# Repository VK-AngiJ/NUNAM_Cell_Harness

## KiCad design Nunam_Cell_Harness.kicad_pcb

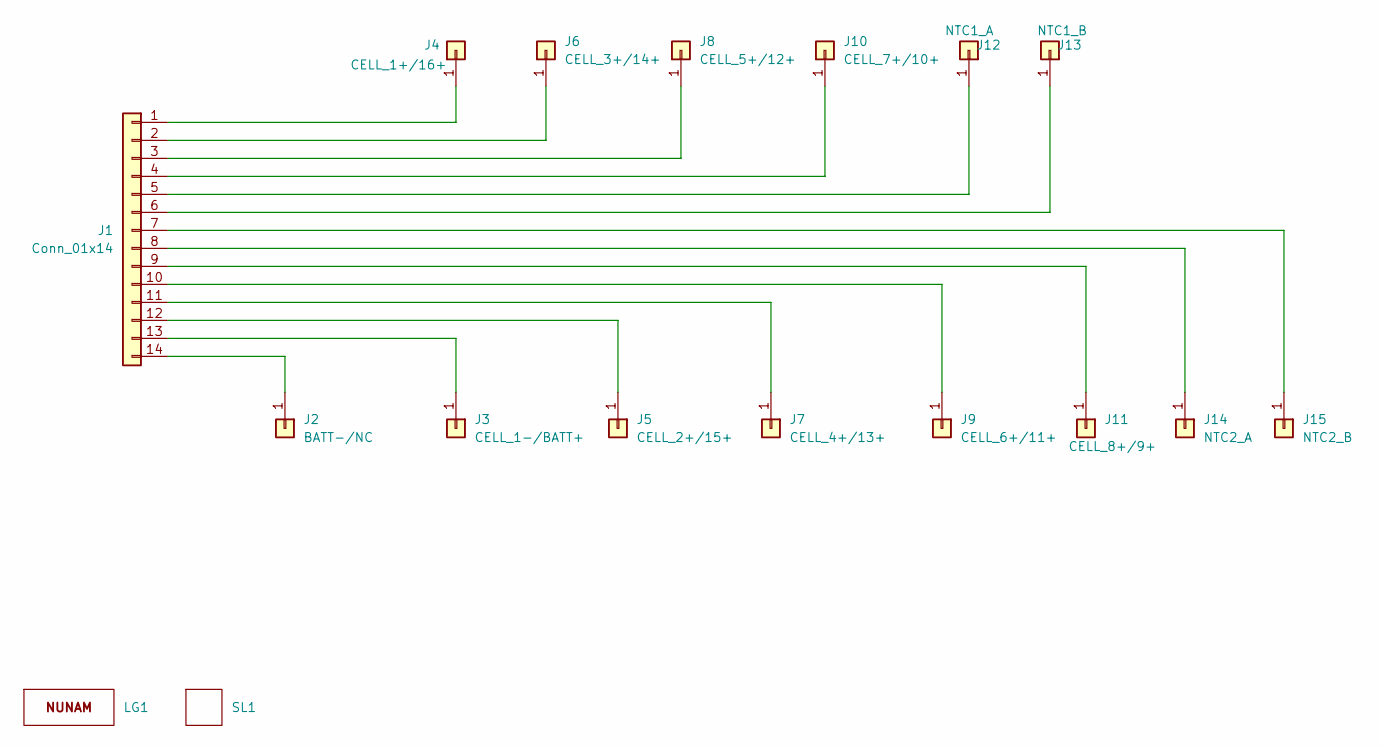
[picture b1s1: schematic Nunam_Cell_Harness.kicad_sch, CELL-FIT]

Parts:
J1: Conn_01x14; JST_XH_S14B-XH-A_1x14_P2.50mm_Horizontal
J2: BATT-/NC; Cell_Pad
J3: CELL_1-/BATT+; Cell_Pad
J4: CELL_1+/16+; Cell_Pad
J5: CELL_2+/15+; Cell_Pad
J6: CELL_3+/14+; Cell_Pad
J7: CELL_4+/13+; Cell_Pad
J8: CELL_5+/12+; Cell_Pad
J9: CELL_6+/11+; Cell_Pad
J10: CELL_7+/10+; Cell_Pad
J11: CELL_8+/9+; Cell_Pad
J12: NTC1_A; Cell_Pad
J13: NTC1_B; Cell_Pad
J14: NTC2_A; Cell_Pad
J15: NTC2_B; Cell_Pad
LG1: Nunam_Logo
SL1: NAME

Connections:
unnamed: J1.1, J4.1 (Pin_1_1)
unnamed: J1.2, J6.1 (Pin_1_1)
unnamed: J1.3, J8.1 (Pin_1_1)
unnamed: J1.4, J10.1 (Pin_1_1)
unnamed: J1.5, J12.1 (Pin_1_1)
unnamed: J1.6, J13.1 (Pin_1_1)
unnamed: J1.7, J15.1 (Pin_1_1)
unnamed: J1.8, J14.1 (Pin_1_1)
unnamed: J1.9, J11.1 (Pin_1_1)
unnamed: J1.10, J9.1 (Pin_1_1)
unnamed: J1.11, J7.1 (Pin_1_1)
unnamed: J1.12, J5.1 (Pin_1_1)
unnamed: J1.13, J3.1 (Pin_1_1)
unnamed: J1.14, J2.1 (Pin_1_1)

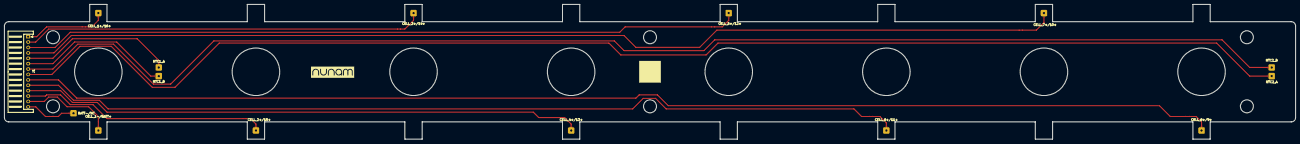
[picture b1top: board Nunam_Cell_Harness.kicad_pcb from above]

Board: 2 copper layers, 598.0 x 62.4 mm, 17 parts (0 on the bottom side), 14 nets.

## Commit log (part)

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2026-06-02 Initial Commmit for NUNAM_CELL_HARNESS
2026-06-02 GERBERs added
